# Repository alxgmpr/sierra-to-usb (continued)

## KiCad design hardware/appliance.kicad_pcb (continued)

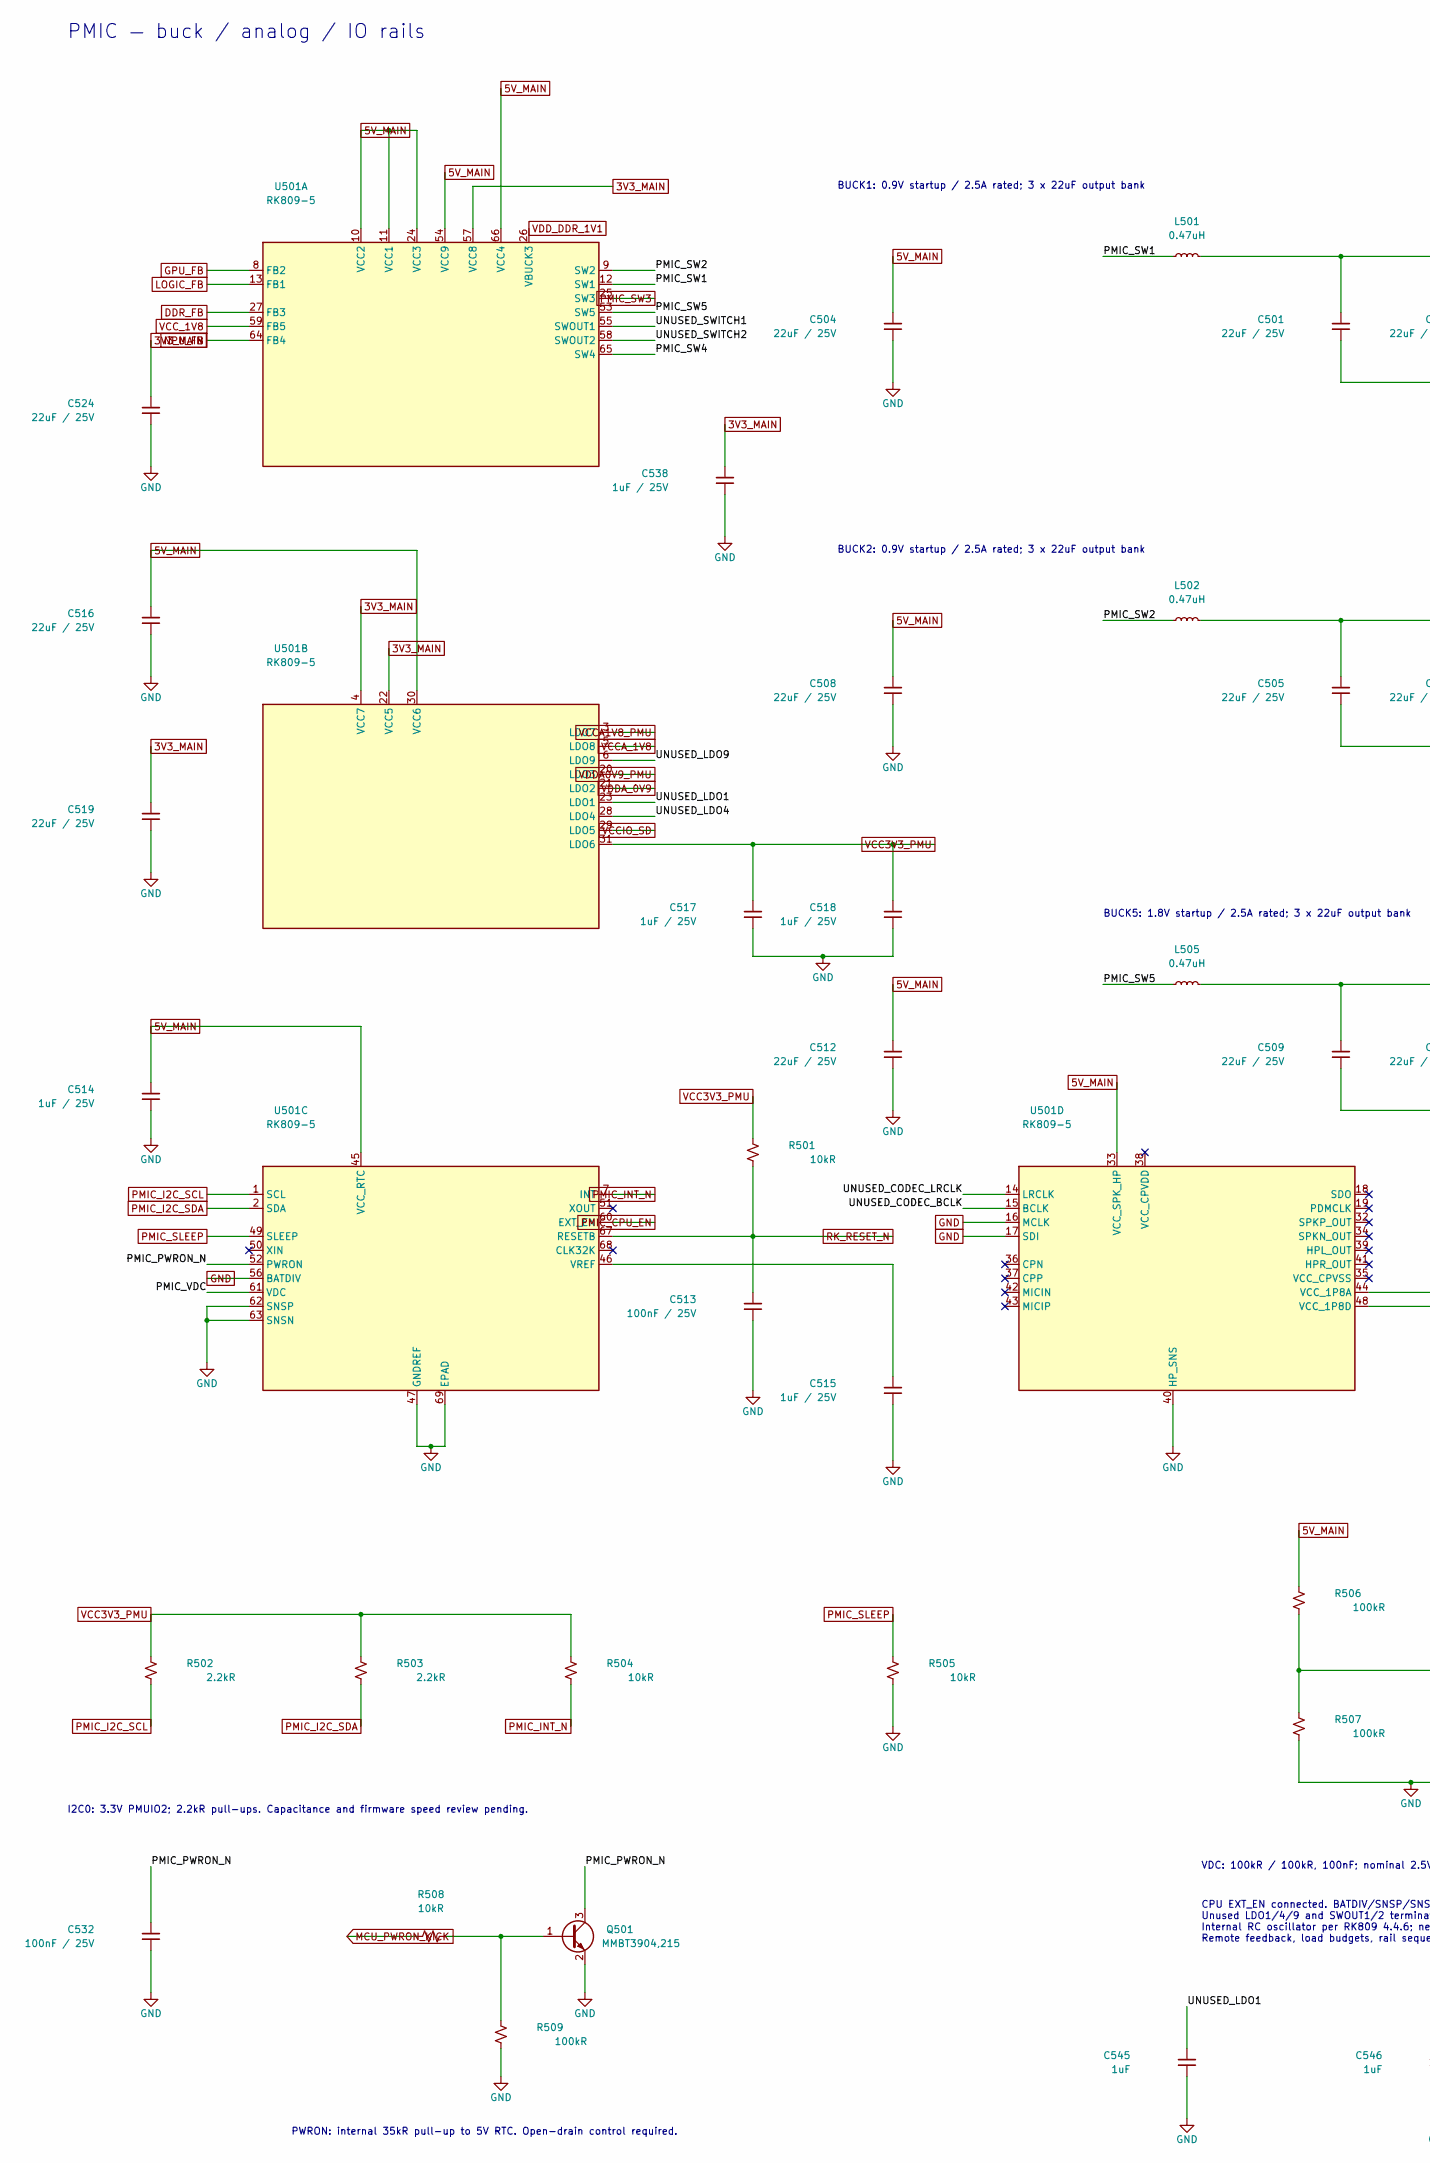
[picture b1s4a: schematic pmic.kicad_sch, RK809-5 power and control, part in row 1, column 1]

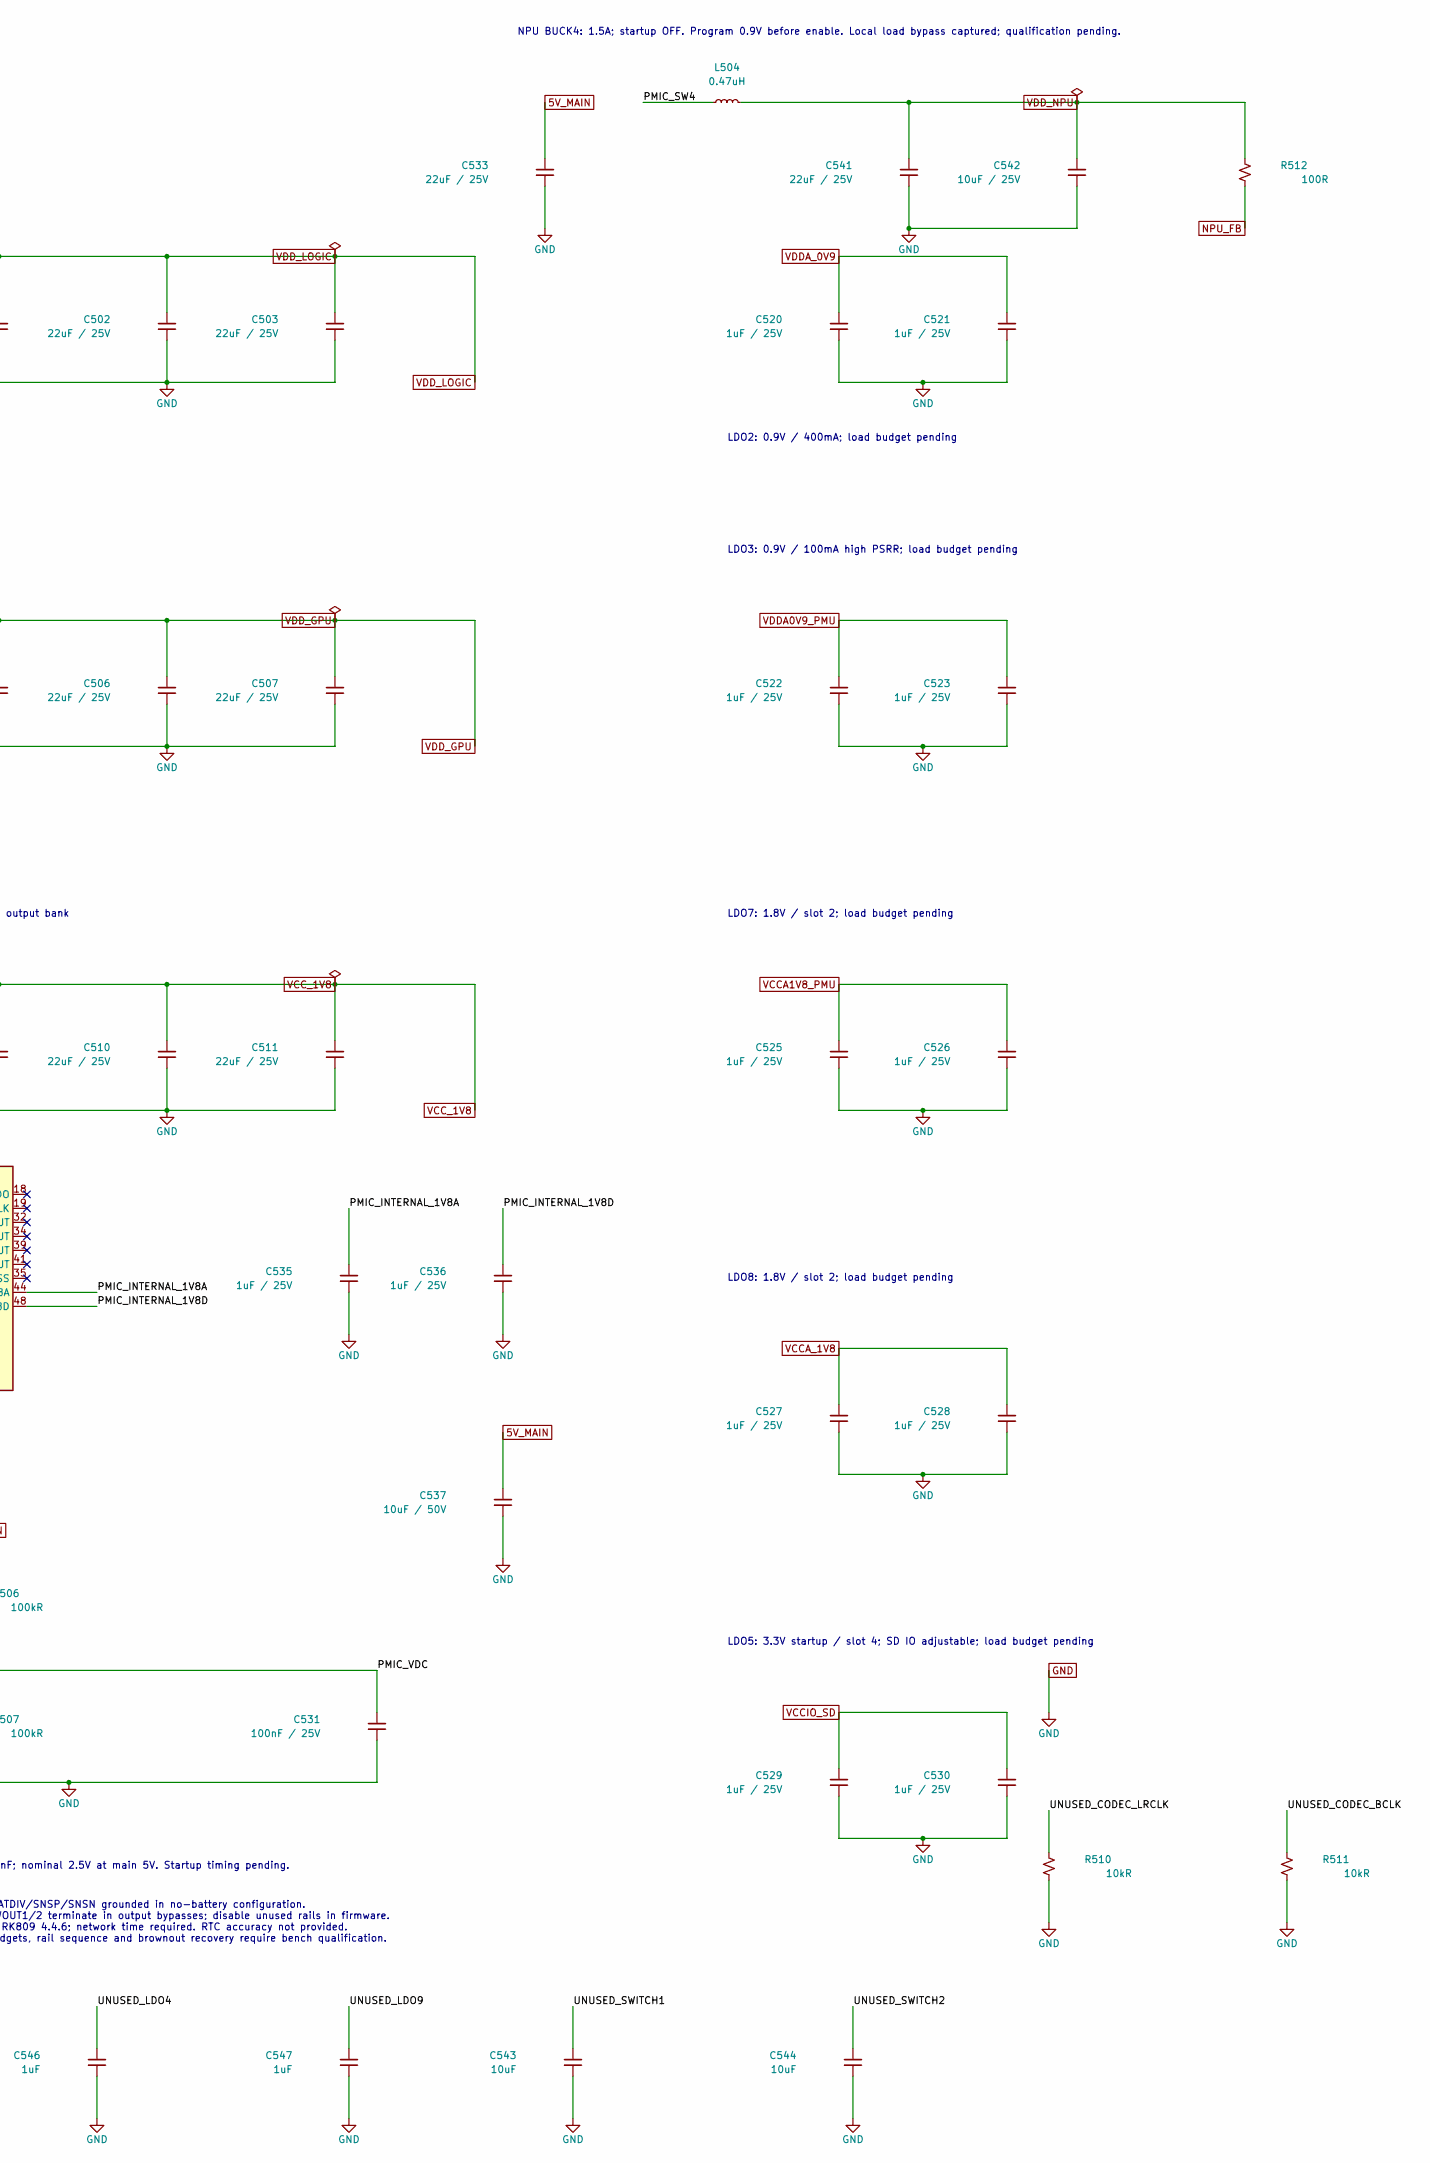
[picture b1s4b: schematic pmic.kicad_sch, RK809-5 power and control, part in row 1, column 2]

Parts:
C501, C502, C503, C504, C505, C506, C507, C508, C509, C510, C511, C512, C516, C519, C524, C533, C541: 22uF / 25V; C_1210_3225Metric_Pad1.33x2.70mm_HandSolder; MPN CL32B226KAJNNNE; LCSC C309062
C513, C531, C532: 100nF / 25V; C_0603_1608Metric_Pad1.08x0.95mm_HandSolder; MPN CL10B104KA8NNNC; LCSC C1590
C514, C515, C517, C518, C520, C521, C522, C523, C525, C526, C527, C528, C529, C530, C535, C536, C538: 1uF / 25V; C_0603_1608Metric_Pad1.08x0.95mm_HandSolder; MPN CL10B105KA8NNNC; LCSC C29936
C537: 10uF / 50V; C_1206_3216Metric_Pad1.33x1.80mm_HandSolder; MPN CL31B106KBHNNNE; LCSC C89632
C542: 10uF / 25V; C_1206_3216Metric_Pad1.33x1.80mm_HandSolder; MPN CL31B106KAHNNNE; LCSC C14860
C543, C544: 10uF; C_1206_3216Metric_Pad1.33x1.80mm_HandSolder; MPN CL31B106KAHNNNE; LCSC C14860
C545, C546, C547: 1uF; C_0603_1608Metric_Pad1.08x0.95mm_HandSolder; MPN CL10B105KA8NNNC; LCSC C29936
L501, L502, L504, L505: 0.47uH; L_Coilcraft_XxL4020; MPN XGL4020-471MEC; LCSC C5837785
Q501: MMBT3904,215; SOT-23_Handsoldering; MPN MMBT3904,215
R501, R504, R505, R508, R510, R511: 10kR; R_0603_1608Metric_Pad0.98x0.95mm_HandSolder; Tolerance 1%; Power Rating 0.1W; MPN RC0603FR-0710KL; LCSC C98220
R502, R503: 2.2kR; R_0603_1608Metric_Pad0.98x0.95mm_HandSolder; Tolerance 1%; Power Rating 0.1W; MPN RC0603FR-072K2L; LCSC C114662
R506, R507, R509: 100kR; R_0603_1608Metric_Pad0.98x0.95mm_HandSolder; Tolerance 1%; Power Rating 0.1W; MPN RC0603FR-07100KL; LCSC C14675
R512: 100R; R_0603_1608Metric_Pad0.98x0.95mm_HandSolder; Tolerance 1%; Power Rating 0.1W; MPN RC0603FR-07100RL; LCSC C105588
U501: RK809-5; ArtInChip_QFN-68-1EP_7x7mm_P0.35mm_EP5.49x5.49mm_ThermalVias; MPN RK809-5; LCSC C2939628

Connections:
3V3_MAIN: C519.1, C524.1, C538.1, U501.4 (VCC7), U501.22 (VCC5), U501.57 (VCC8); also elsewhere on the board
5V_MAIN: C504.1, C508.1, C512.1, C514.1, C516.1, C533.1, C537.1, R506.1, U501.10 (VCC2), U501.11 (VCC1), U501.24 (VCC3), U501.30 (VCC6), U501.33 (VCC_SPK_HP), U501.45 (VCC_RTC), U501.54 (VCC9), U501.66 (VCC4); also elsewhere on the board
/Processor PMIC/PMIC_INTERNAL_1V8A: C535.1, U501.44 (VCC_1P8A)
/Processor PMIC/PMIC_INTERNAL_1V8D: C536.1, U501.48 (VCC_1P8D)
/Processor PMIC/PMIC_PWRON_N: C532.1, Q501.3 (C), U501.52 (PWRON)
/Processor PMIC/PMIC_SW1: L501.1, U501.12 (SW1)
/Processor PMIC/PMIC_SW2: L502.1, U501.9 (SW2)
/Processor PMIC/PMIC_SW4: L504.1, U501.65 (SW4)
/Processor PMIC/PMIC_SW5: L505.1, U501.53 (SW5)
/Processor PMIC/PMIC_VDC: C531.1, R506.2, R507.1, U501.61 (VDC)
/Processor PMIC/UNUSED_CODEC_BCLK: R511.1, U501.15 (BCLK)
/Processor PMIC/UNUSED_CODEC_LRCLK: R510.1, U501.14 (LRCLK)
/Processor PMIC/UNUSED_LDO1: C545.1, U501.23 (LDO1)
/Processor PMIC/UNUSED_LDO4: C546.1, U501.28 (LDO4)
/Processor PMIC/UNUSED_LDO9: C547.1, U501.6 (LDO9)
/Processor PMIC/UNUSED_SWITCH1: C543.1, U501.55 (SWOUT1)
/Processor PMIC/UNUSED_SWITCH2: C544.1, U501.58 (SWOUT2)
DDR_FB: U501.27 (FB3); also elsewhere on the board
GND: C501.2, C502.2, C503.2, C504.2, C505.2, C506.2, C507.2, C508.2, C509.2, C510.2, C511.2, C512.2, C513.2, C514.2, C515.2, C516.2, C517.2, C518.2, C519.2, C520.2, C521.2, C522.2, C523.2, C524.2, C525.2, C526.2, C527.2, C528.2, C529.2, C530.2, C531.2, C532.2, C533.2, C535.2, C536.2, C537.2, C538.2, C541.2, C542.2, C543.2, C544.2, C545.2, C546.2, C547.2, Q501.2 (E), R505.2, R507.2, R509.2, R510.2, R511.2, U501.16 (MCLK), U501.17 (SDI), U501.40 (HP_SNS), U501.47 (GNDREF), U501.56 (BATDIV), U501.62 (SNSP), U501.63 (SNSN), U501.69 (EPAD); also elsewhere on the board
GPU_FB: U501.8 (FB2); also elsewhere on the board
LOGIC_FB: U501.13 (FB1); also elsewhere on the board
MCU_PWRON_KICK: R508.1; also elsewhere on the board
NPU_FB: R512.2, U501.64 (FB4); also elsewhere on the board
unnamed: Q501.1 (B), R508.2, R509.1
unnamed: C515.1, U501.46 (VREF)
PMIC_CPU_EN: U501.60 (EXT_EN); also elsewhere on the board
PMIC_I2C_SCL: R502.2, U501.1 (SCL); also elsewhere on the board
PMIC_I2C_SDA: R503.2, U501.2 (SDA); also elsewhere on the board
PMIC_INT_N: R504.2, U501.7 (INT); also elsewhere on the board
PMIC_SLEEP: R505.1, U501.49 (SLEEP); also elsewhere on the board
PMIC_SW3: U501.25 (SW3); also elsewhere on the board
RK_RESET_N: C513.1, R501.2, U501.67 (RESETB); also elsewhere on the board
VCC3V3_PMU: C517.1, C518.1, R501.1, R502.1, R503.1, R504.1, U501.31 (LDO6); also elsewhere on the board
VCCA1V8_PMU: C525.1, C526.1, U501.3 (LDO7); also elsewhere on the board
VCCA_1V8: C527.1, C528.1, U501.5 (LDO8); also elsewhere on the board
VCCIO_SD: C529.1, C530.1, U501.29 (LDO5); also elsewhere on the board
VCC_1V8: C509.1, C510.1, C511.1, L505.2, U501.59 (FB5); also elsewhere on the board
VDDA0V9_PMU: C522.1, C523.1, U501.20 (LDO3); also elsewhere on the board
VDDA_0V9: C520.1, C521.1, U501.21 (LDO2); also elsewhere on the board
VDD_DDR_1V1: U501.26 (VBUCK3); also elsewhere on the board
VDD_GPU: C505.1, C506.1, C507.1, L502.2; also elsewhere on the board
VDD_LOGIC: C501.1, C502.1, C503.1, L501.2; also elsewhere on the board
VDD_NPU: C541.1, C542.1, L504.2, R512.1; also elsewhere on the board

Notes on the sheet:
LDO7: 1.8V / slot 2; load budget pending
LDO2: 0.9V / 400mA; load budget pending
LDO3: 0.9V / 100mA high PSRR; load budget pending
VDC: 100kR / 100kR, 100nF; nominal 2.5V at main 5V. Startup timing pending.
PWRON: internal 35kR pull-up to 5V RTC. Open-drain control required.
BUCK2: 0.9V startup / 2.5A rated; 3 x 22uF output bank
CPU EXT_EN connected. BATDIV/SNSP/SNSN grounded in no-battery configuration. Unused LDO1/4/9 and SWOUT1/2 terminate in output bypasses; disable unused rails in firmware. Internal RC oscillator per RK809 4.4.6; network time required. RTC accuracy not provided. Remote feedback, load budgets, rail seq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
LDO8: 1.8V / slot 2; load budget pending
LDO5: 3.3V startup / slot 4; SD IO adjustable; load budget pending
I2C0: 3.3V PMUIO2; 2.2kR pull-ups. Capacitance and firmware speed review pending.
PMIC — buck / analog / IO rails
NPU BUCK4: 1.5A; startup OFF. Program 0.9V before enable. Local load bypass captured; qualification pending.
BUCK1: 0.9V startup / 2.5A rated; 3 x 22uF output bank
BUCK5: 1.8V startup / 2.5A rated; 3 x 22uF output bank

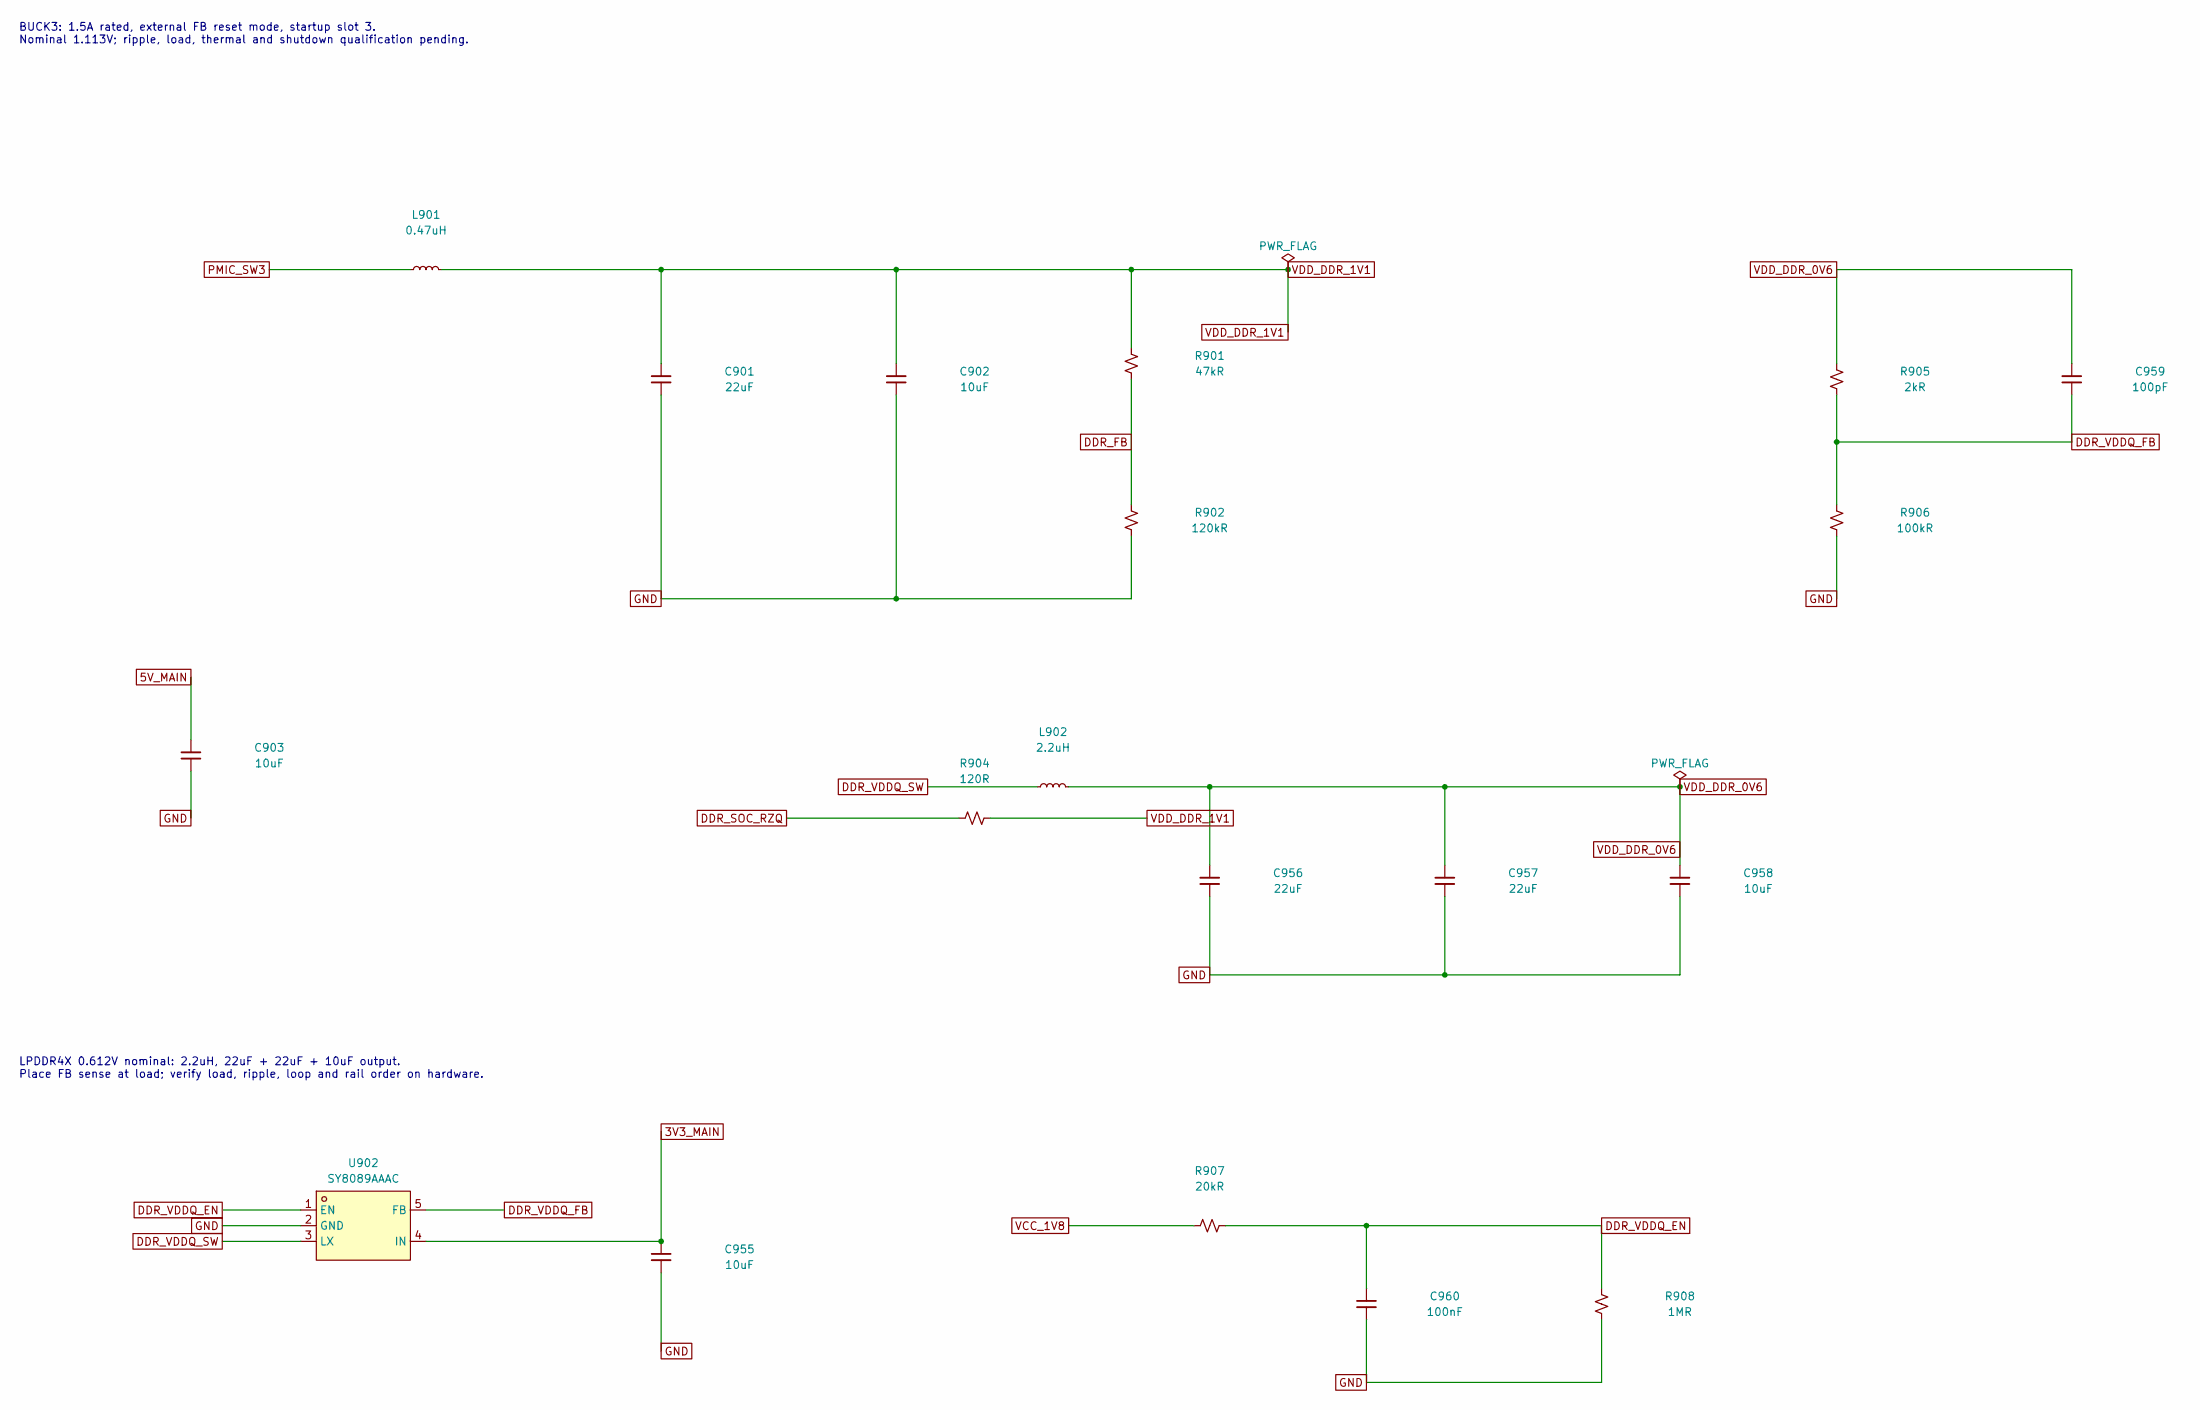
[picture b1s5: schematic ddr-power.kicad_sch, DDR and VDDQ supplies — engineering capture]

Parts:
C901, C956, C957: 22uF; C_1210_3225Metric_Pad1.33x2.70mm_HandSolder; Voltage Rating 25V; MPN CL32B226KAJNNNE; LCSC C309062
C902, C903, C955, C958: 10uF; C_1206_3216Metric_Pad1.33x1.80mm_HandSolder; Voltage Rating 25V; MPN CL31B106KAHNNNE; LCSC C14860
C959: 100pF; C_0603_1608Metric_Pad1.08x0.95mm_HandSolder; Voltage Rating 50V; Tolerance 5%; MPN CL10C101JB8NNNC; LCSC C14858
C960: 100nF; C_0603_1608Metric_Pad1.08x0.95mm_HandSolder; Voltage Rating 25V; Tolerance 10%; MPN CL10B104KA8NNNC; LCSC C1590
L901: 0.47uH; L_Coilcraft_XxL4020; MPN XGL4020-471MEC; LCSC C5837785
L902: 2.2uH; L_Coilcraft_XxL4020; Inductance Tolerance 20%; MPN XGL4020-222MEC
R901: 47kR; R_0603_1608Metric_Pad0.98x0.95mm_HandSolder; Tolerance 1%; Power Rating 0.1W; MPN RC0603FR-0747KL; LCSC C105579
R902: 120kR; R_0603_1608Metric_Pad0.98x0.95mm_HandSolder; Tolerance 1%; Power Rating 0.1W; MPN RC0603FR-07120KL; LCSC C114607
R904: 120R; R_0603_1608Metric_Pad0.98x0.95mm_HandSolder; Tolerance 1%; Power Rating 0.1W; MPN RC0603FR-07120RL; LCSC C114640
R905: 2kR; R_0603_1608Metric_Pad0.98x0.95mm_HandSolder; Tolerance 1%; Power Rating 0.1W; MPN RC0603FR-072KL; LCSC C105576
R906: 100kR; R_0603_1608Metric_Pad0.98x0.95mm_HandSolder; Tolerance 1%; Power Rating 0.1W; MPN RC0603FR-07100KL; LCSC C14675
R907: 20kR; R_0603_1608Metric_Pad0.98x0.95mm_HandSolder; Tolerance 1%; Power Rating 0.1W; MPN RC0603FR-0720KL; LCSC C105575
R908: 1MR; R_0603_1608Metric_Pad0.98x0.95mm_HandSolder; Tolerance 1%; Power Rating 0.1W; MPN RC0603FR-071ML; LCSC C105578
U902: SY8089AAAC; SOT-23-5_HandSoldering; MPN SY8089AAAC; LCSC C78988

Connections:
3V3_MAIN: C955.1, U902.4 (IN); also elsewhere on the board
5V_MAIN: C903.1; also elsewhere on the board
DDR_FB: R901.2, R902.1; also elsewhere on the board
DDR_SOC_RZQ: R904.1; also elsewhere on the board
DDR_VDDQ_EN: C960.1, R907.2, R908.1, U902.1 (EN)
DDR_VDDQ_FB: C959.2, R905.2, R906.1, U902.5 (FB)
DDR_VDDQ_SW: L902.1, U902.3 (LX)
GND: C901.2, C902.2, C903.2, C955.2, C956.2, C957.2, C958.2, C960.2, R902.2, R906.2, R908.2, U902.2 (GND); also elsewhere on the board
PMIC_SW3: L901.1; also elsewhere on the board
VCC_1V8: R907.1; also elsewhere on the board
VDD_DDR_0V6: C956.1, C957.1, C958.1, C959.1, L902.2, R905.1; also elsewhere on the board
VDD_DDR_1V1: C901.1, C902.1, L901.2, R901.1, R904.2; also elsewhere on the board

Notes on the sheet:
BUCK3: 1.5A rated, external FB reset mode, startup slot 3. Nominal 1.113V; ripple, load, thermal and shutdown qualification pending.
LPDDR4X 0.612V nominal: 2.2uH, 22uF + 22uF + 10uF output. Place FB sense at load; verify load, ripple, loop and rail order on hardware.
